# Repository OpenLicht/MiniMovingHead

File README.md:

# Moving Head

## Pinout

## Protocol
Length is 3 bytes, command byte followed by two value bytes  
| command | value(high) | value(low)|

### Example
Set led_0 brightness to 100%  
Bytes to send: 0x70 0x00 0x64

## State select
|Command | State|
|--------|------|
|0x91 | Manual movement|
|0x92 | Position regulation|

## Manual movement
|Command | Value | Action |
|--------|-------|--------|
|0x41 | 0x00 | move bottom servo clockwise|
|0x42 | 0x00 | move bottom servo anticlockwise|
|0x45 | 0x01 ... 0x10 | set bottom servo speed [1 - 10]|
|0x51 | 0x00 | move top servo anticlockwise|
|0x52 | 0x00 | move top servo clockwise|
|0x70 | 0x00 ... 0x64 | set led_0 brightness [0 - 100 %]|
|0x71 | 0x00 ... 0x64 | set led_1 brightness [0 - 100 %]|
|0x72 | 0x00 ... 0x64 | set led_2 brightness [0 - 100 %]|
|0x73 | 0x00 ... 0x64 | set led_3 brightness [0 - 100 %]|
|0x90 | 0x00 | stop bottom servo|

## Position regulation
|Command | Value | Action|
|--------|-------|--------|
|0x60 | 0x00 ... 0x168 | move bottom servo to position [0 - 360°]|
|0x61 | 0x00 ... 0xB4 | move top servo to position [0 - 180°]|
|0x70 | 0x00 ... 0x64 | set led_0 brightness [0 - 100 %]|
|0x71 | 0x00 ... 0x64 | set led_1 brightness [0 - 100 %]|
|0x72 | 0x00 ... 0x64 | set led_2 brightness [0 - 100 %]|
|0x73 | 0x00 ... 0x64 | set led_3 brightness [0 - 100 %]|

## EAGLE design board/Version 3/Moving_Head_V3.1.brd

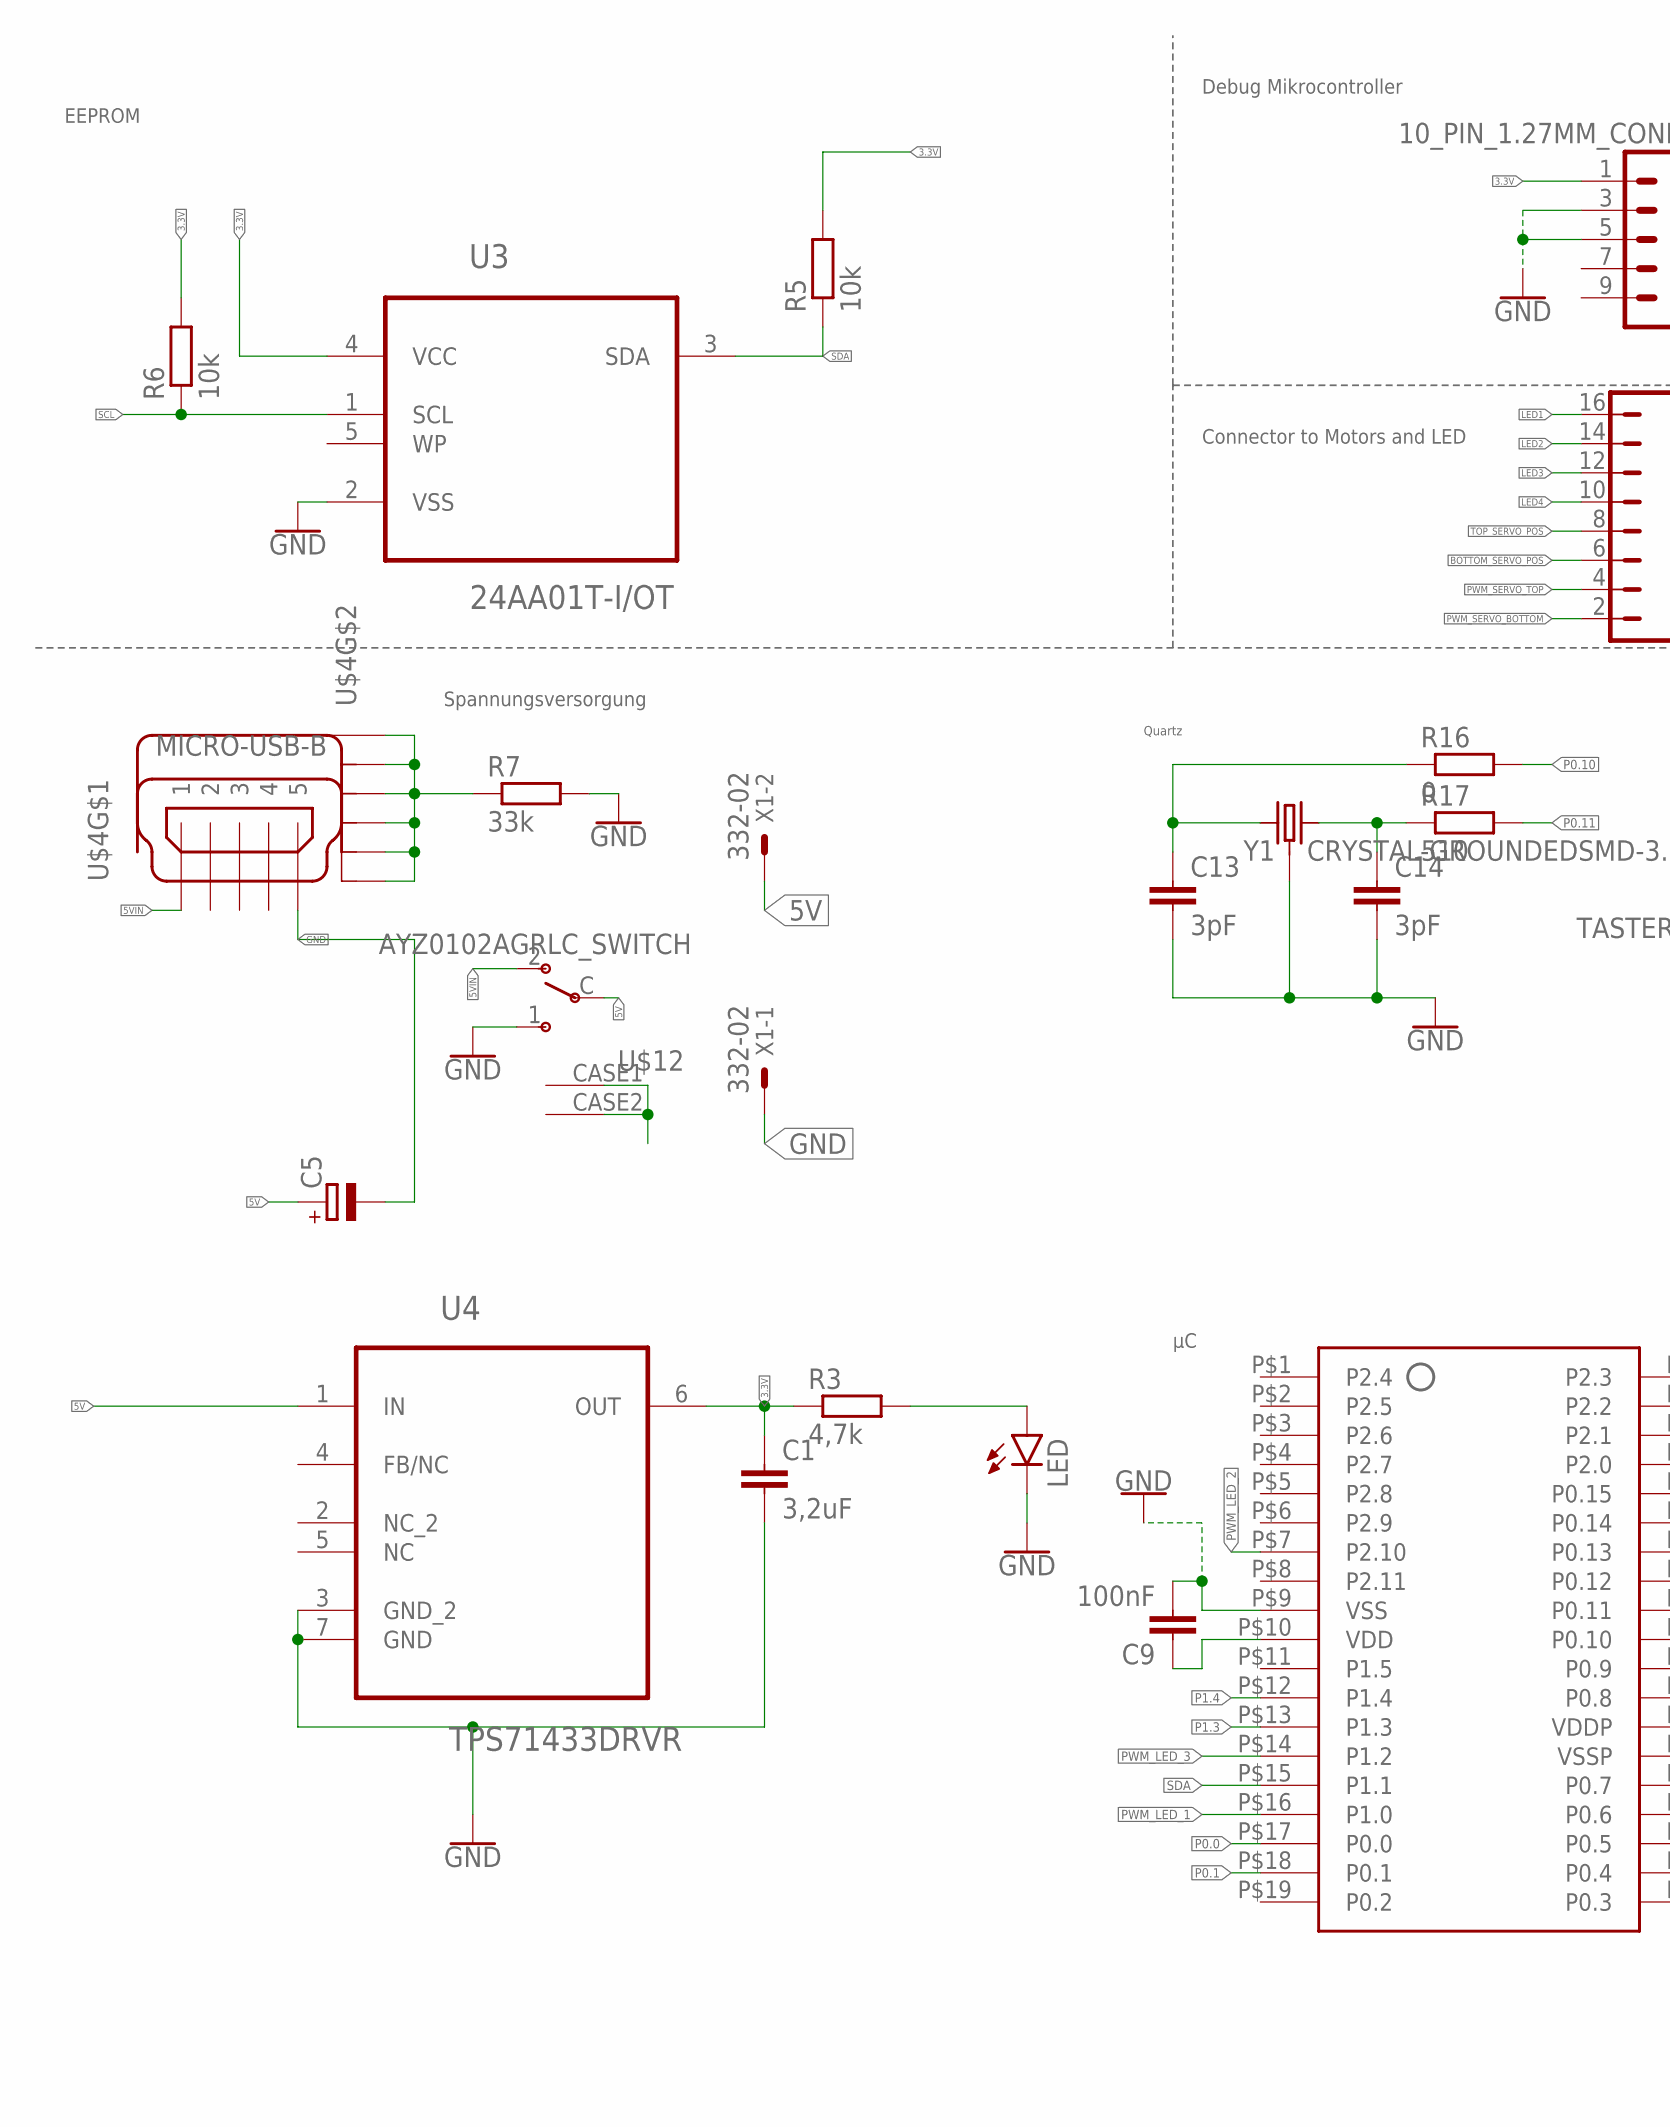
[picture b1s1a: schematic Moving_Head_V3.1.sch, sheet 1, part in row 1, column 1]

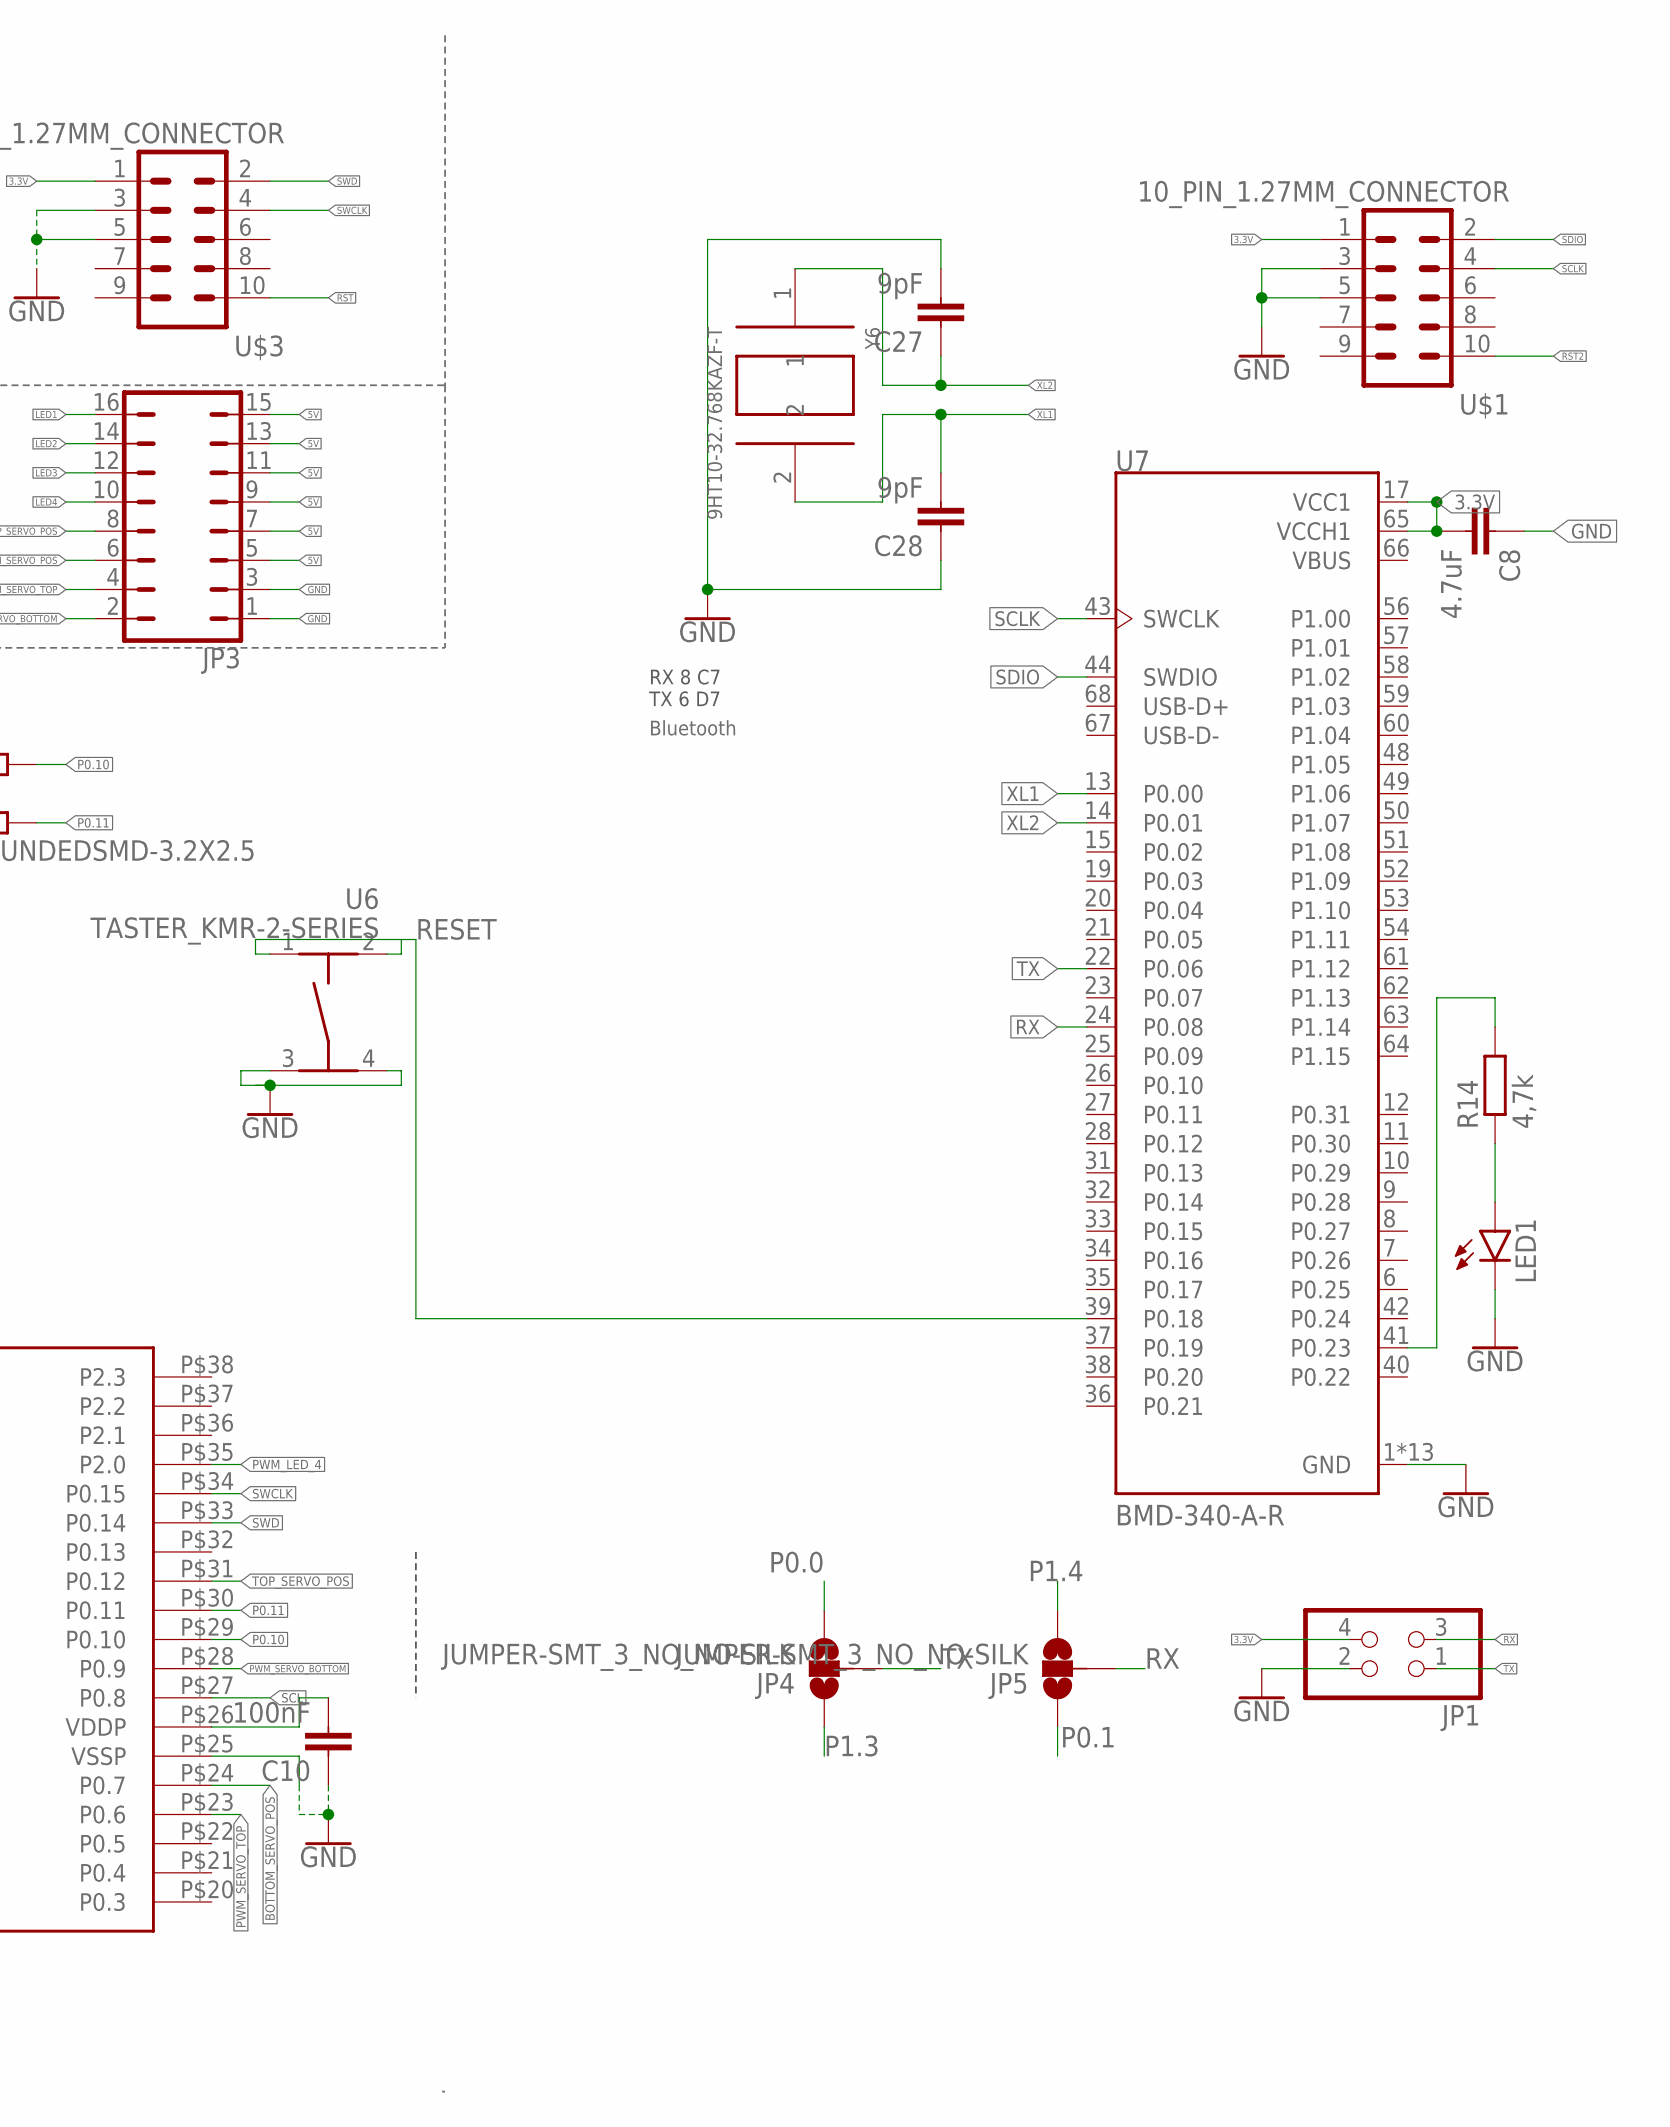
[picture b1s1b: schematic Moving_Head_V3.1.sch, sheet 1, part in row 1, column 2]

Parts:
C1: 3,2uF; C0805
C5: CPOL-EUB/3528-21R; B/3528-21R
C8: 4.7uF; C0805
C9, C10: 100nF; C0805
C13, C14: 3pF; C0805
C27, C28: 9pF; C0805
JP1: PINHD-2X2; 2X02
JP3: JUMPER_JP8Q
JP4, JP5: JUMPER-SMT_3_NO_NO-SILK; SMT-JUMPER_3_NO_NO-SILK
LED: LEDCHIPLED_0805; CHIPLED_0805
LED1: SML-H12V8TT86; CHIPLED_0805
R3, R14: 4,7k; R0805
R5, R6: 10k; R0805
R7: 33k; R0805
R16: 0; R0805
R17: 510; R0805
U3: 24AA01T-I/OT; SOT95P270X145-5N
U4: TPS71433DRVR; SON65P200X200X80-7N
U5: XMC1400_38P
U6: TASTER_KMR-2-SERIES; KMR-2-SERIES
U7: BMD-340-A-R; RIGADO_BMD-340-A-R
U$1, U$3: 10_PIN_1.27MM_CONNECTOR; 10_PIN_1.27MM
U$4: MICRO-USB-B; MICRO_USB_B
U$12: AYZ0102AGRLC_SWITCH; AYZ0102AGRLC
X1: 332-02
Y1: CRYSTAL-GROUNDEDSMD-3.2X2.5; CRYSTAL-SMD-3.2X2.5MM
Y6: 9HT10-32.768KAZF-T; XTAL320X150X75

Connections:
3.3V: C1.1, C8.2, C9.1, C10.2, JP1.4, R3.1, R5.2, R6.2, U3.4 (VCC), U4.6 (OUT), U5.P$10 (VDD), U5.P$26 (VDDP), U7.17 (VCC1), U7.65 (VCCH1), U$1.1, U$3.1; also elsewhere on the board
5V: C5.+, JP3.5, JP3.7, JP3.9, JP3.11, JP3.13, JP3.15, U4.1 (IN), U$12.C, X1.2; also elsewhere on the board
5VIN: U$4.1, U$12.2
BOTTOM_SERVO_POS: JP3.6, U5.P$24 (P0.7)
GND: C1.2, C5.-, C8.1, C9.2, C10.1, C13.2, C14.2, C27.2, C28.1, JP1.2, JP3.1, JP3.3, LED.C, LED1.C, R7.2, U3.2 (VSS), U4.3 (GND_2), U4.7 (GND), U5.P$9 (VSS), U5.P$25 (VSSP), U6.3, U6.4, U7.1 (GND), U7.2 (GND), U7.3 (GND), U7.4 (GND), U7.5 (GND), U7.16 (GND), U7.18 (GND), U7.29 (GND), U7.30 (GND), U7.45 (GND), U7.46 (GND), U7.47 (GND), U7.55 (GND), U$1.3, U$1.5, U$3.3, U$3.5, U$4.5, U$12.1, U$12.CASE1, U$12.CASE2, X1.1, Y1.2 (3), Y1.4 (3); also elsewhere on the board
LED1: JP3.16; also elsewhere on the board
LED2: JP3.14; also elsewhere on the board
LED3: JP3.12; also elsewhere on the board
LED4: JP3.10; also elsewhere on the board
unnamed: R14.2, U7.41 (P0.23)
unnamed: LED1.A, R14.1
unnamed: LED.A, R3.2
unnamed: R7.1, U$4.P$1 (S1), U$4.P$2 (S2), U$4.P$6 (S3), U$4.P$7 (S4), U$4.P$9 (S5), U$4.P$10 (S6)
unnamed: C14.1, R17.1, Y1.3 (2)
unnamed: C13.1, R16.1, Y1.1
P0.0: JP4.3, U5.P$17 (P0.0)
P0.1: JP5.1, U5.P$18 (P0.1)
P0.10: R16.2, U5.P$29 (P0.10)
P0.11: R17.2, U5.P$30 (P0.11)
P1.3: JP4.1, U5.P$13 (P1.3)
P1.4: JP5.3, U5.P$12 (P1.4)
PWM_LED_1: U5.P$16 (P1.0); also elsewhere on the board
PWM_LED_2: U5.P$7 (P2.10); also elsewhere on the board
PWM_LED_3: U5.P$14 (P1.2); also elsewhere on the board
PWM_LED_4: U5.P$35 (P2.0); also elsewhere on the board
PWM_SERVO_BOTTOM: JP3.2, U5.P$28 (P0.9)
PWM_SERVO_TOP: JP3.4, U5.P$23 (P0.6)
RESET: U6.1, U6.2, U7.39 (P0.18)
RST: U$3.10
RST2: U$1.10
RX: JP1.3, JP5.2, U7.24 (P0.08)
SCL: R6.1, U3.1 (SCL), U5.P$27 (P0.8)
SCLK: U7.43 (SWCLK), U$1.4
SDA: R5.1, U3.3 (SDA), U5.P$15 (P1.1)
SDIO: U7.44 (SWDIO), U$1.2
SWCLK: U5.P$34 (P0.15), U$3.4
SWD: U5.P$33 (P0.14), U$3.2
TOP_SERVO_POS: JP3.8, U5.P$31 (P0.12)
TX: JP1.1, JP4.2, U7.22 (P0.06)
VBUS: U7.66 (VBUS)
XL1: C28.2, U7.13 (P0.00), Y6.2
XL2: C27.1, U7.14 (P0.01), Y6.1

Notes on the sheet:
Spannungsversorgung
Connector to Motors and LED
Debug Mikrocontroller
EEPROM
Quartz
Bluetooth
RX 8 C7 TX 6 D7

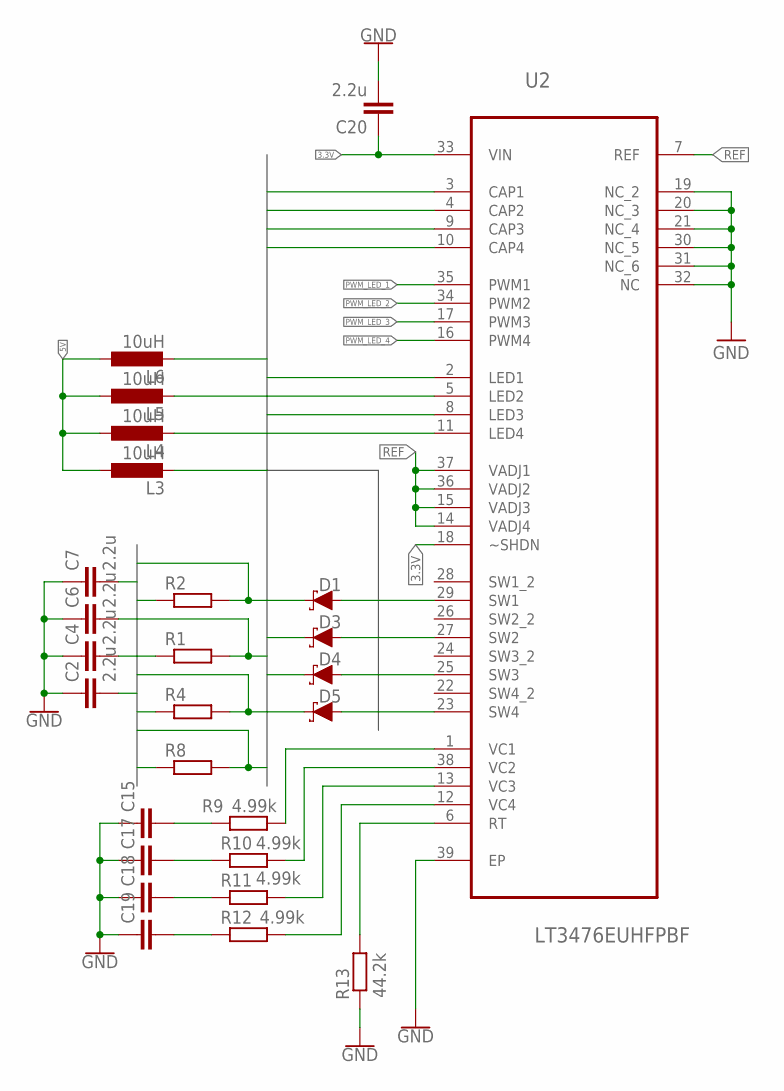
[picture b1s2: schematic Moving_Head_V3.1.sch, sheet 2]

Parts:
C2, C4, C6, C7, C20: 2.2u; C0805
C15, C17, C18, C19: 2.2n; C0805
D1, D3, D4, D5: 1A/23V/620mV; SOD-323
L3, L4, L5, L6: 10uH; L2012C
R1, R2, R4, R8: 300m; M0805
R9, R10, R11, R12: 4.99k; M0805
R13: 44.2k; M0805
U2: LT3476EUHFPBF; QFN50P500X700X80-39N

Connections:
3.3V: C20.1, U2.18 (~SHDN), U2.33 (VIN); also elsewhere on the board
5V: L3.1, L4.1, L5.1, L6.1; also elsewhere on the board
CAP1: C7.2, D1.C, R2.2, U2.3 (CAP1)
CAP2: C6.2, D3.C, R1.2, U2.4 (CAP2)
CAP3: C4.2, D4.C, R4.2, U2.9 (CAP3)
CAP4: C2.2, D5.C, R8.2, U2.10 (CAP4)
GND: C2.1, C4.1, C6.1, C7.1, C15.1, C17.1, C18.1, C19.1, C20.2, R13.1, U2.19 (NC_2), U2.20 (NC_3), U2.21 (NC_4), U2.30 (NC_5), U2.31 (NC_6), U2.32 (NC), U2.39 (EP); also elsewhere on the board
LED1: R2.1, U2.2 (LED1); also elsewhere on the board
LED2: R1.1, U2.5 (LED2); also elsewhere on the board
LED3: R4.1, U2.8 (LED3); also elsewhere on the board
LED4: R8.1, U2.11 (LED4); also elsewhere on the board
unnamed: R9.2, U2.1 (VC1)
unnamed: R10.2, U2.38 (VC2)
unnamed: R11.2, U2.13 (VC3)
unnamed: R12.2, U2.12 (VC4)
unnamed: R13.2, U2.6 (RT)
unnamed: C15.2, R9.1
unnamed: C17.2, R10.1
unnamed: C18.2, R11.1
unnamed: C19.2, R12.1
PWM_LED_1: U2.35 (PWM1); also elsewhere on the board
PWM_LED_2: U2.34 (PWM2); also elsewhere on the board
PWM_LED_3: U2.17 (PWM3); also elsewhere on the board
PWM_LED_4: U2.16 (PWM4); also elsewhere on the board
REF: U2.7 (REF), U2.14 (VADJ4), U2.15 (VADJ3), U2.36 (VADJ2), U2.37 (VADJ1)
SW1: D1.A, L6.2, U2.29 (SW1)
SW2: D3.A, L5.2, U2.27 (SW2)
SW3: D4.A, L4.2, U2.25 (SW3)
SW4: D5.A, L3.2, U2.23 (SW4)

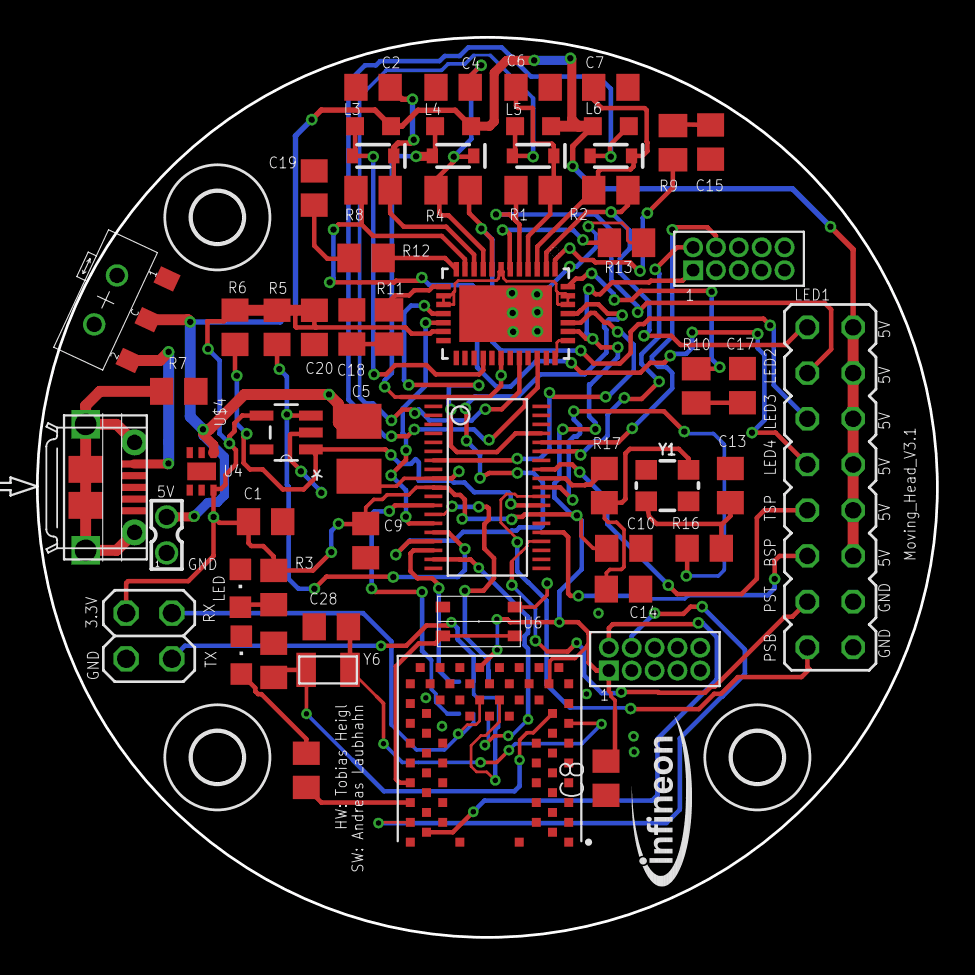
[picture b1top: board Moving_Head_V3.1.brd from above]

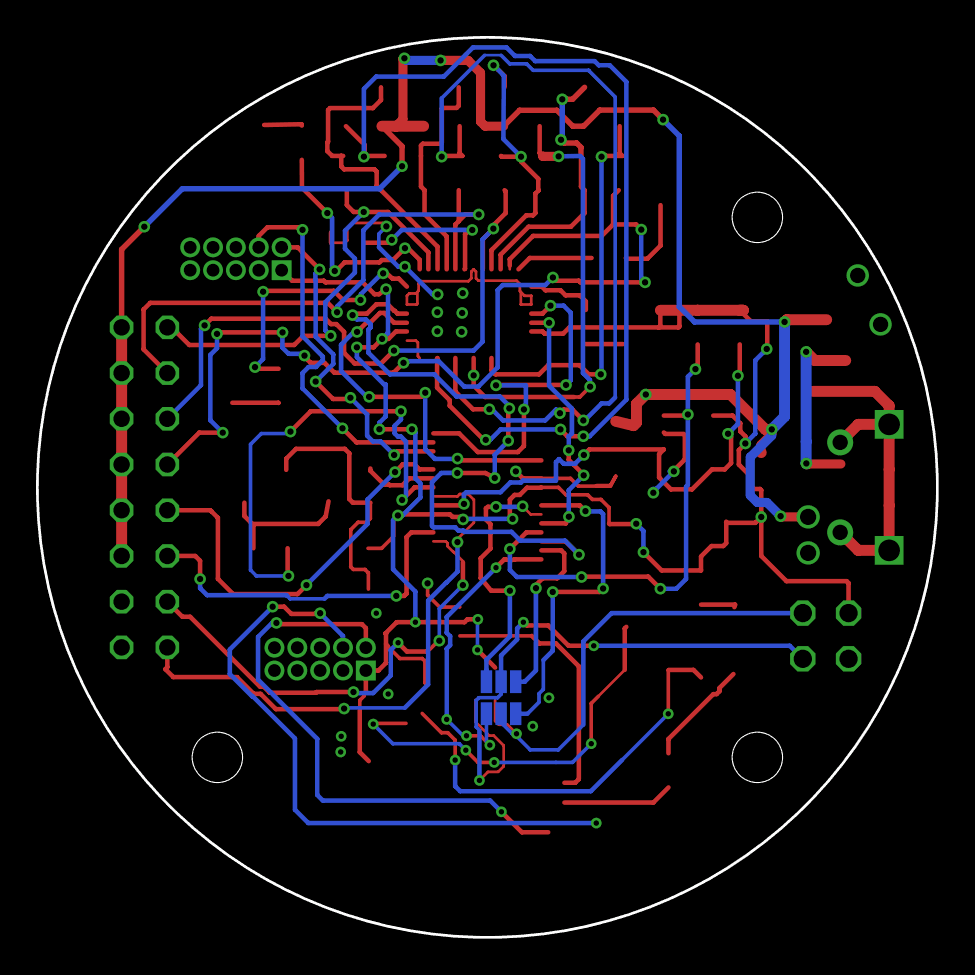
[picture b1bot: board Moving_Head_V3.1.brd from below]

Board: 2 copper layers, 50.0 x 50.0 mm, 64 parts (2 on the bottom side), 57 nets.

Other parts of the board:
U$5, U$6, U$8: 2,8

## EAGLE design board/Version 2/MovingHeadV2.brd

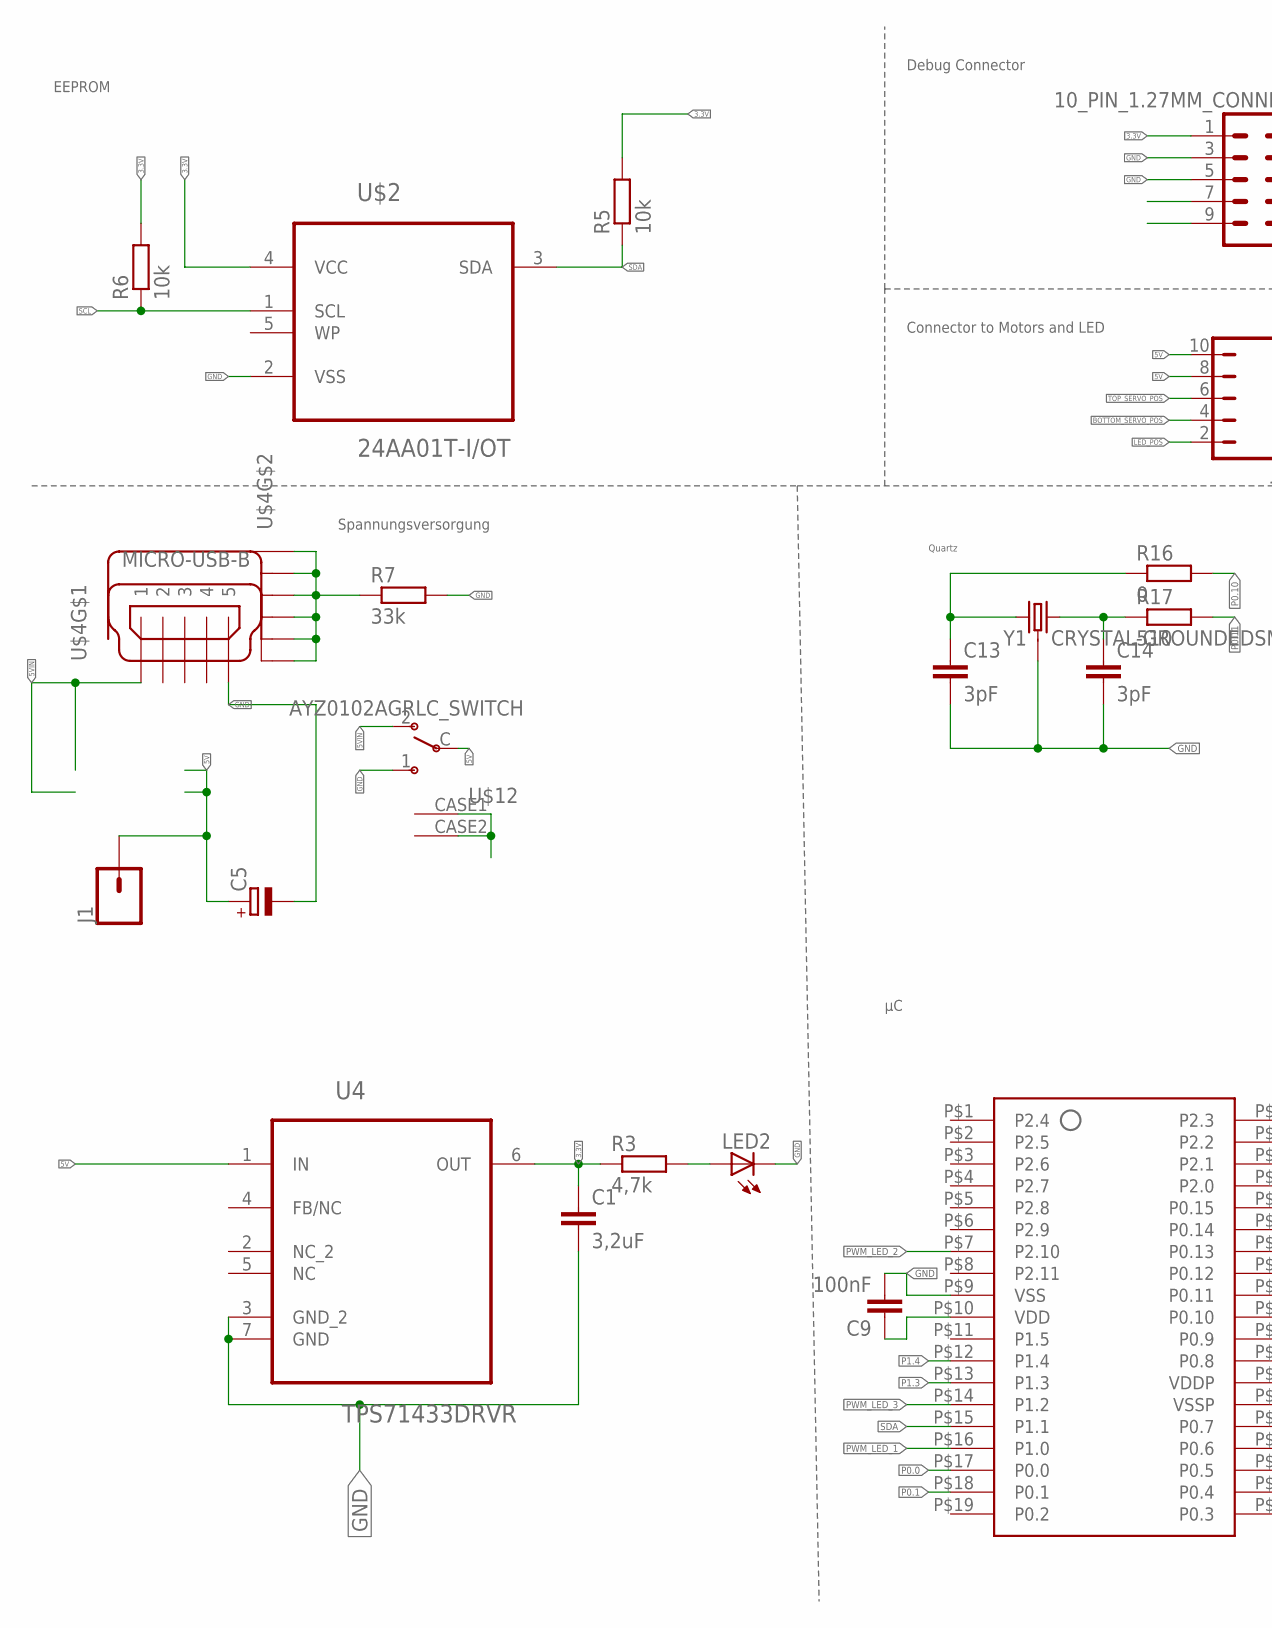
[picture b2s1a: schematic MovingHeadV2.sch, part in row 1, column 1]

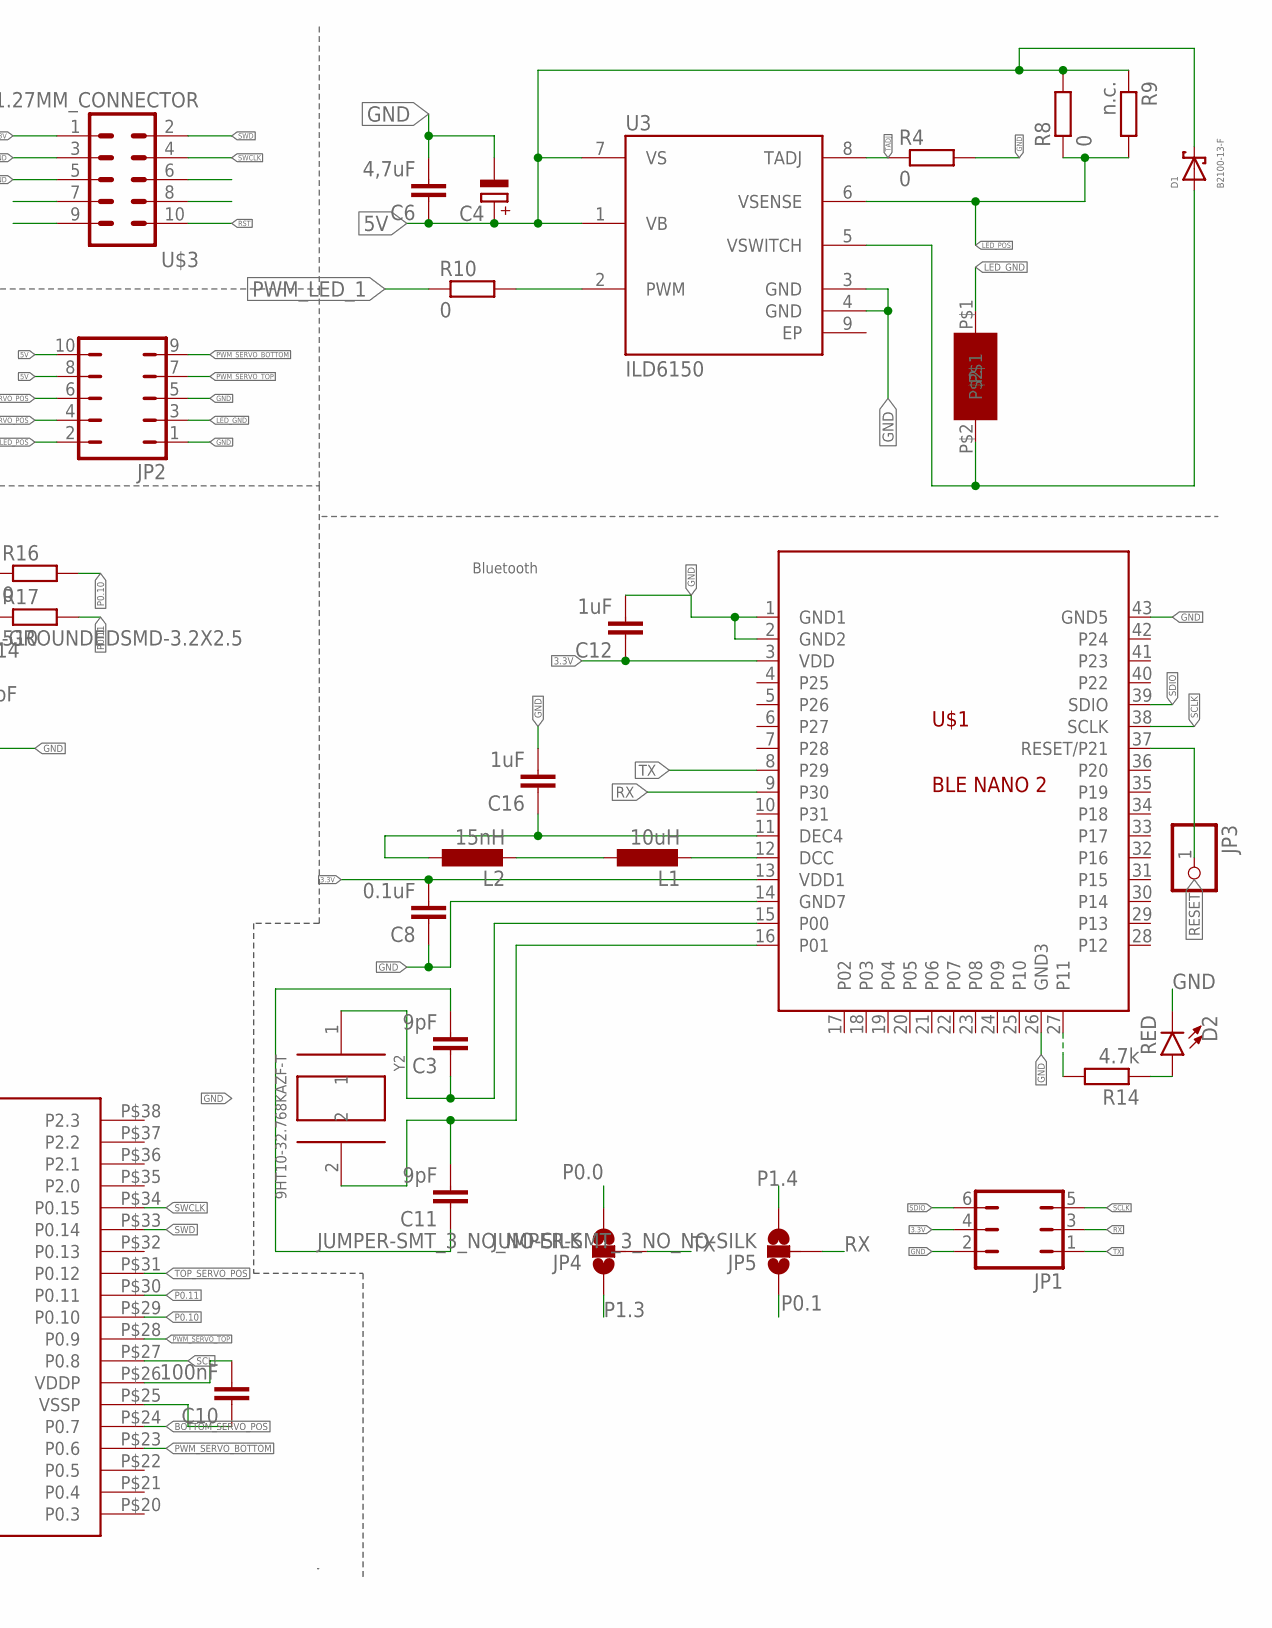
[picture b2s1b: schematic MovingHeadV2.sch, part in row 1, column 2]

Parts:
C1: 3,2uF; C0805
C3, C11: 9pF; C0805
C4: CPOL-EUD; PANASONIC_D
C5: CPOL-EUB/3528-21R; B/3528-21R
C6: 4,7uF; C0805
C8: 0.1uF; C0805
C9, C10: 100nF; C0805
C12, C16: 1uF; C0603
C13, C14: 3pF; C0805
D1: B2100-13-F; SMB
D2: RED; LED-0603
J1: CONN_01; 1X01
JP1: JP3Q
JP2: JP5Q
JP3: PINHD-1X1; 1X01
JP4, JP5: JUMPER-SMT_3_NO_NO-SILK; SMT-JUMPER_3_NO_NO-SILK
L1: 10uH; L2012C
L2: 15nH; L2012C
LED2: LEDCHIPLED_0805; CHIPLED_0805
R3: 4,7k; R0805
R4, R8, R10, R16: 0; R0805
R5, R6: 10k; R0805
R7: 33k; R0805
R9: n.c.; R0805
R14: 4.7k; R0805
R17: 510; R0805
U3: ILD6150; SOIC127P600X170-9N-V2
U4: TPS71433DRVR; SON65P200X200X80-7N
U$1: BLE NANO 2; RBT07
U$2: 24AA01T-I/OT; SOT95P270X145-5N
U$3: 10_PIN_1.27MM_CONNECTOR; 10_PIN_1.27MM
U$4: MICRO-USB-B; MICRO_USB_B
U$7: CUSTOMCOIL6.8UH
U$10: XMC1400_38P
U$12: AYZ0102AGRLC_SWITCH; AYZ0102AGRLC
Y1: CRYSTAL-GROUNDEDSMD-3.2X2.5; CRYSTAL-SMD-3.2X2.5MM
Y2: 9HT10-32.768KAZF-T; XTAL320X150X75

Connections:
3.3V: C1.1, C8.2, C9.1, C10.2, C12.1, JP1.4, R3.1, R5.2, R6.2, U4.6 (OUT), U$1.3 (VDD), U$1.13 (VDD1), U$2.4 (VCC), U$3.1, U$10.P$10 (VDD), U$10.P$26 (VDDP)
5V: C4.+, C5.+, C6.1, D1.C, J1.1, JP2.8, JP2.10, R8.2, R9.1, U3.1 (VB), U3.7 (VS), U4.1 (IN), U$12.C
5VIN: U$4.1, U$12.2
BOTTOM_SERVO_POS: JP2.4, U$10.P$24 (P0.7)
EP: U3.9 (EP)
GND: C1.2, C3.2, C4.-, C5.-, C6.2, C8.1, C9.2, C10.1, C11.1, C12.2, C13.2, C14.2, C16.2, D2.C, JP1.2, JP2.1, JP2.5, LED2.C, R4.2, R7.2, U3.3 (GND), U3.4 (GND), U4.3 (GND_2), U4.7 (GND), U$1.1 (GND1), U$1.2 (GND2), U$1.14 (GND7), U$1.26 (GND3), U$1.43 (GND5), U$2.2 (VSS), U$3.3, U$3.5, U$4.5, U$10.P$9 (VSS), U$10.P$25 (VSSP), U$12.1, U$12.CASE1, U$12.CASE2, Y1.2 (3), Y1.4 (3)
LED_GND: JP2.3, U$7.P$1
LED_POS: JP2.2, R8.1, R9.2, U3.6 (VSENSE)
unnamed: R10.2, U3.2 (PWM)
unnamed: D2.A, R14.1
unnamed: LED2.A, R3.2
unnamed: R7.1, U$4.P$1 (S1), U$4.P$2 (S2), U$4.P$6 (S3), U$4.P$7 (S4), U$4.P$9 (S5), U$4.P$10 (S6)
unnamed: D1.A, U3.5 (VSWITCH), U$7.P$2
unnamed: C14.1, R17.1, Y1.3 (2)
unnamed: C13.1, R16.1, Y1.1
unnamed: L1.2, U$1.12 (DCC)
unnamed: L1.1, L2.2
unnamed: C16.1, L2.1, U$1.11 (DEC4)
unnamed: C3.1, U$1.15 (P00), Y2.1
unnamed: C11.2, U$1.16 (P01), Y2.2
unnamed: R14.2, U$1.27 (P11)
P0.0: JP4.3, U$10.P$17 (P0.0)
P0.1: JP5.1, U$10.P$18 (P0.1)
P0.10: R16.2, U$10.P$29 (P0.10)
P0.11: R17.2, U$10.P$30 (P0.11)
P1.3: JP4.1, U$10.P$13 (P1.3)
P1.4: JP5.3, U$10.P$12 (P1.4)
PWM_LED_1: R10.1, U$10.P$16 (P1.0)
PWM_LED_2: U$10.P$7 (P2.10)
PWM_LED_3: U$10.P$14 (P1.2)
PWM_SERVO_BOTTOM: JP2.9, U$10.P$23 (P0.6)
PWM_SERVO_TOP: JP2.7, U$10.P$28 (P0.9)
RESET: JP3.1, U$1.37 (RESET/P21)
RST: U$3.10
RX: JP1.3, JP5.2, U$1.9 (P30)
SCL: R6.1, U$2.1 (SCL), U$10.P$27 (P0.8)
SCLK: JP1.5, U$1.38 (SCLK)
SDA: R5.1, U$2.3 (SDA), U$10.P$15 (P1.1)
SDIO: JP1.6, U$1.39 (SDIO)
SWCLK: U$3.4, U$10.P$34 (P0.15)
SWD: U$3.2, U$10.P$33 (P0.14)
TADJ: R4.1, U3.8 (TADJ)
TOP_SERVO_POS: JP2.6, U$10.P$31 (P0.12)
TX: JP1.1, JP4.2, U$1.8 (P29)

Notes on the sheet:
Bluetooth
Spannungsversorgung
Connector to Motors and LED
Debug Connector
EEPROM
Quartz

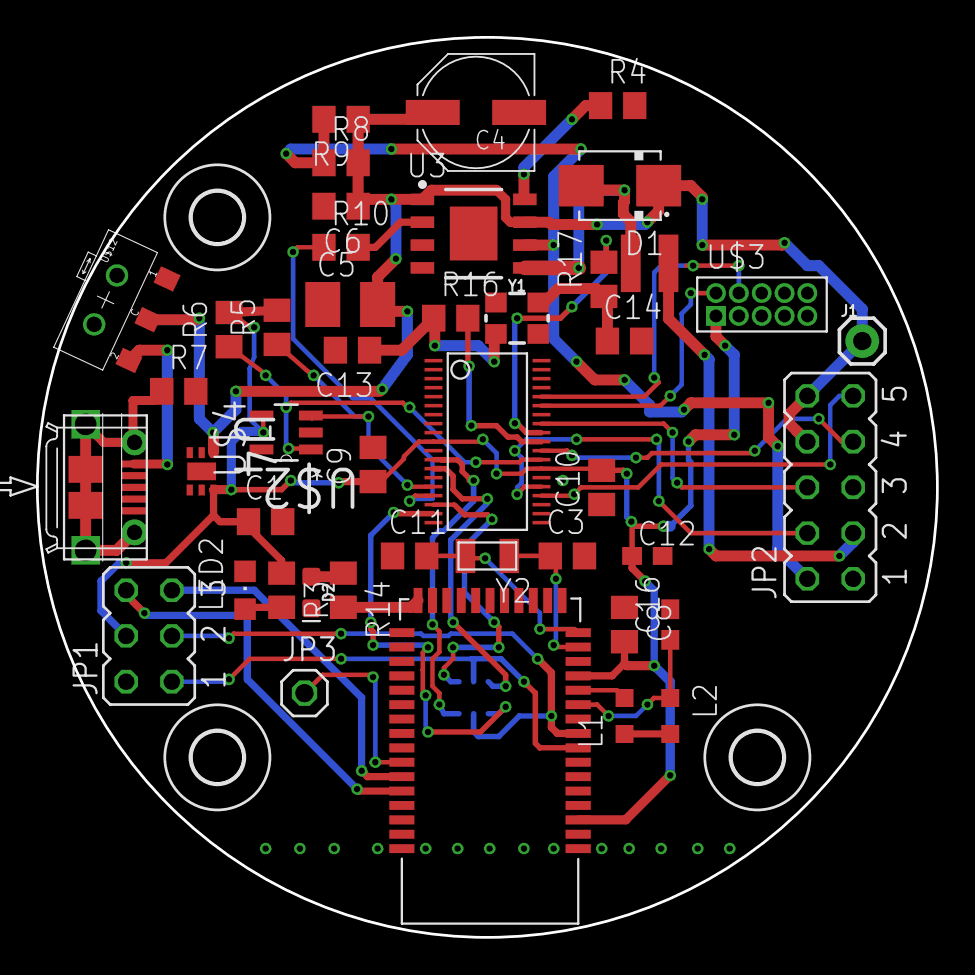
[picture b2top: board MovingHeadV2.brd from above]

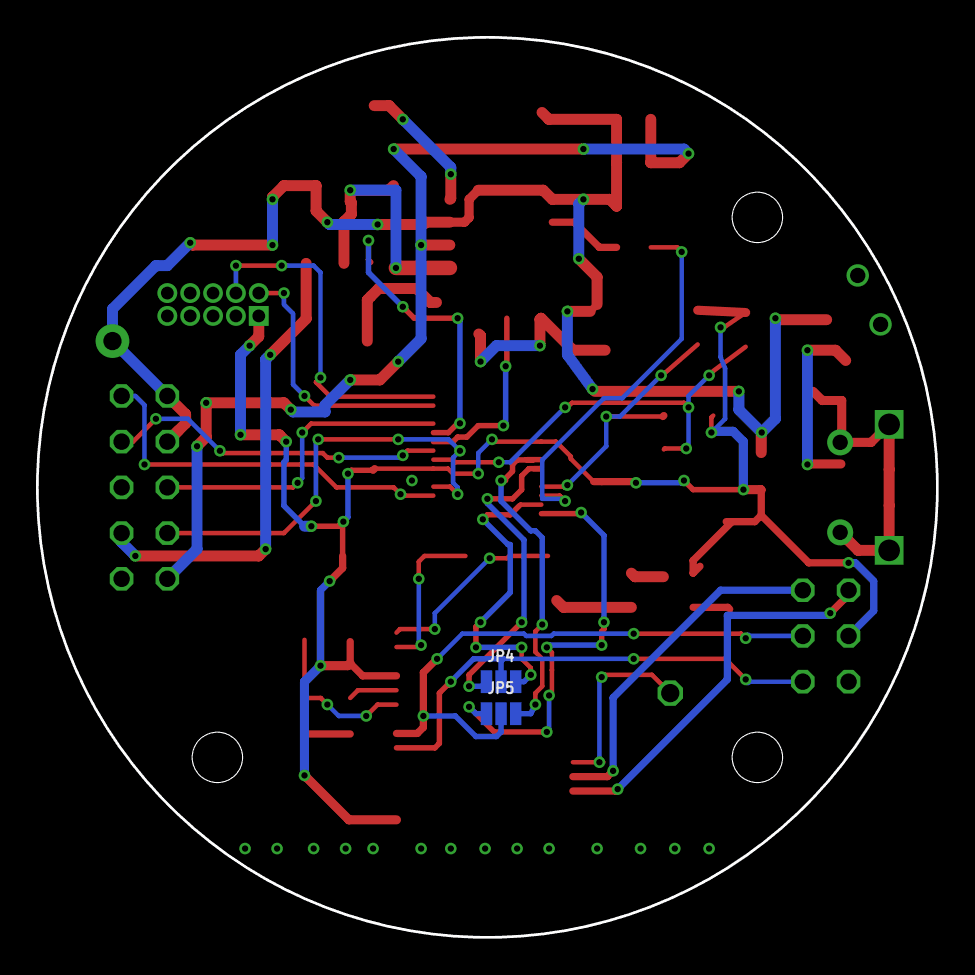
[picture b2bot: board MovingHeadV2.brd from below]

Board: 2 copper layers, 50.0 x 50.0 mm, 49 parts (2 on the bottom side), 40 nets.

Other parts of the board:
U$5, U$6, U$8: 2,8

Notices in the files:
parts and their libraries:
SparkFun-Connectors: Licensing: Creative Commons ShareAlike 4.0 International - https://creativecommons.org/licenses/by-sa/4.0
